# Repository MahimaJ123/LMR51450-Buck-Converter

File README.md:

# LMR51450-Buck-Converter
PCB design of LMR51450-based Buck Converter

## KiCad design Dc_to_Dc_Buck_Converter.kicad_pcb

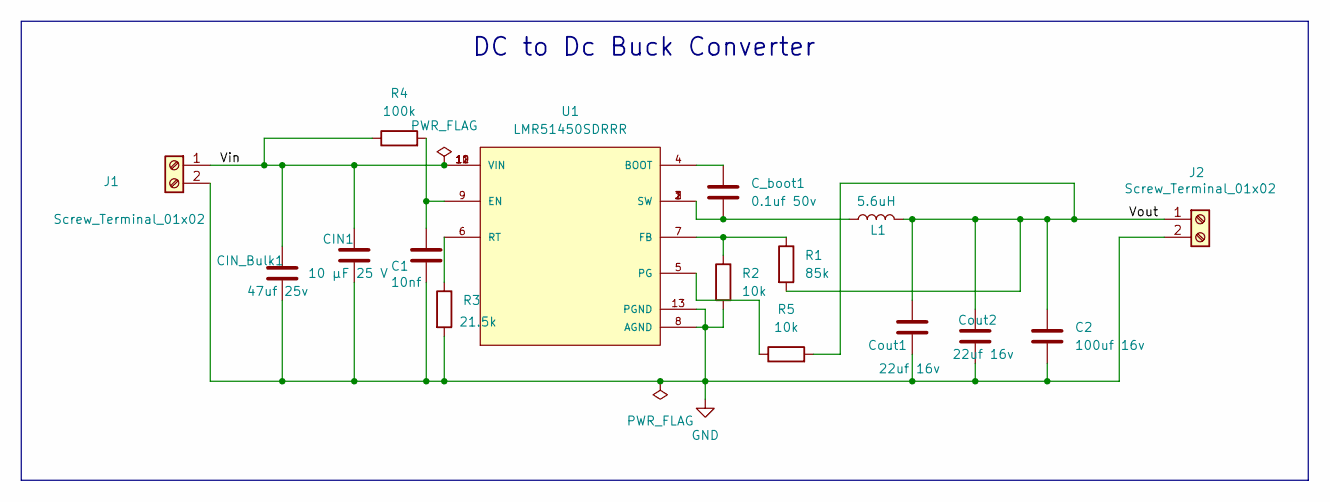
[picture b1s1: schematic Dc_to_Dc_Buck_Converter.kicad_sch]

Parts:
C1: 10nf; C_0603_1608Metric
C2: 100uf 16v; C_Elec_6.3x7.7
CIN1: 10 µF 25 V; C_0805_2012Metric
CIN_Bulk1: 47uf 25v; C_Elec_6.3x5.4
C_boot1: 0.1uf 50v; C_0603_1608Metric
Cout1, Cout2: 22uf 16v; C_0805_2012Metric
J1, J2: Screw_Terminal_01x02; TerminalBlock_Phoenix_MKDS-1,5-2-5.08_1x02_P5.08mm_Horizont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
L1: 5.6uH; L_7.3x7.3_H3.5
R1: 85k; R_0805_2012Metric
R2, R5: 10k; R_0805_2012Metric
R3: 21.5k; R_0805_2012Metric
R4: 100k; R_0805_2012Metric
U1: LMR51450SDRRR; CONV_LMR51450SDRRR; PARTREV December 2022; DigiKey_Part_Number 296-LMR51450SDRRRCT-ND

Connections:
/Vin: CIN1.1, CIN_Bulk1.1, J1.1, R4.1, U1.10 (VIN), U1.11 (VIN), U1.12 (VIN)
/Vout: C2.1, Cout1.1, Cout2.1, J2.1, L1.2, R1.2, R5.2
GND: C1.2, C2.2, CIN1.2, CIN_Bulk1.2, Cout1.2, Cout2.2, J1.2, J2.2, R2.2, R3.2, U1.8 (AGND), U1.13 (PGND), U1.14, U1.15, U1.16
unnamed 3: C_boot1.2, L1.1, U1.1 (SW), U1.2 (SW), U1.3 (SW); also elsewhere on the board
unnamed 4: C_boot1.1, U1.4 (BOOT); also elsewhere on the board
unnamed: C1.1, R4.2, U1.9 (EN)
unnamed: R1.1, R2.1, U1.7 (FB)
unnamed: R5.1, U1.5 (PG)
unnamed: R3.1, U1.6 (RT)

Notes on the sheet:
DC to Dc Buck Converter

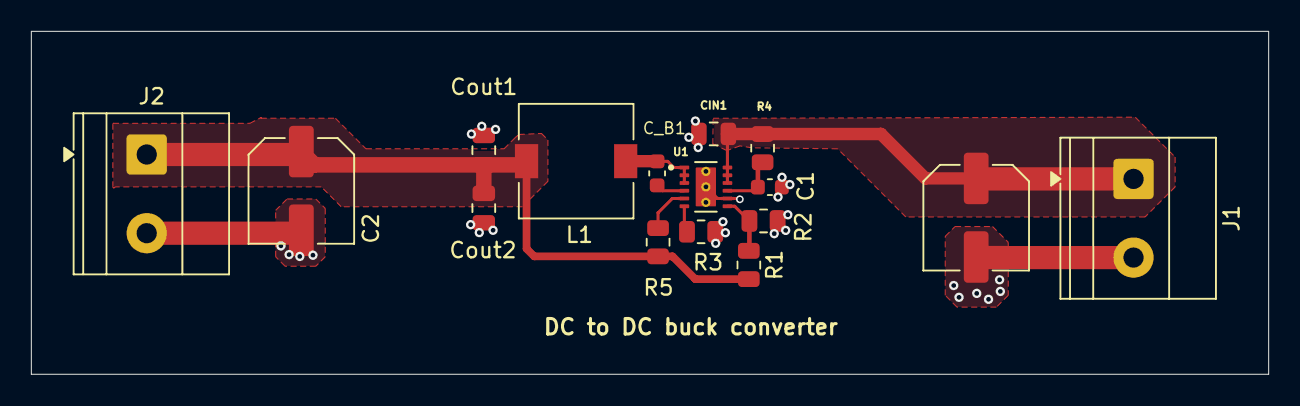
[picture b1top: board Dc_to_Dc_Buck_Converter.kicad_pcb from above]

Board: 2 copper layers, 79.9 x 22.1 mm, 16 parts (0 on the bottom side), 9 nets.

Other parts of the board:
C_B1: 0.1uf 50v; C_0603_1608Metric

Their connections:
unnamed 3: C_B1.2; also elsewhere on the board
unnamed 4: C_B1.1; also elsewhere on the board

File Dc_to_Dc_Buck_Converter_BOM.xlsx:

Designator | Quantity | Footprint | Value / Description
U1 | 1 | CONV_LMR51450SDRRR | LMR51450SDRRR (buck regulator IC)
J1, J2 | 2 | TerminalBlock_Phoenix_MKDS-5-2-5.08_1x02_P5.08mm_Horizontal | 2-pin screw terminal, 5.08 mm pitch (rated ≥6 A)
L1 | 1 | L_7.3x7.3_H3.5 | 5.6 µH inductor, Isat ≥ 8 A, low DCR
Cout1, Cout2 | 2 | C_0805_2012Metric | 22 µF, 16 V, X7R MLCC
R5, R2 | 2 | R_0805_2012Metric | 10 kΩ, 1%
R4 | 1 | R_0805_2012Metric | 100 kΩ, 1%
R3 | 1 | R_0805_2012Metric | 21.5 kΩ, 1% (RT resistor for fSW)
R1 | 1 | R_0805_2012Metric | 85 kΩ, 1% (feedback)
C_B1 | 1 | C_0603_1608Metric | 0.1 µF, 50 V, X7R (bootstrap cap)
CIN_Bulk1 | 1 | C_Elec_6.3x5.4 | 47 µF, 25 V, polymer electrolytic (input bulk)
CIN1 | 1 | C_0805_2012Metric | 10 µF, 25 V, MLCC (input decoupling)
C2 | 1 | C_Elec_6.3x7.7 | 100 µF, 16 V, polymer bulk (output bulk)
C1 | 1 | C_0603_1608Metric | 10 nF, 50 V (small decoupling cap)

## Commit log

2025-09-16 add media folder for images
